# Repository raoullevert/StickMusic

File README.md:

# StickMusic
Stick USB Radio FM/AM/MP3 Diy

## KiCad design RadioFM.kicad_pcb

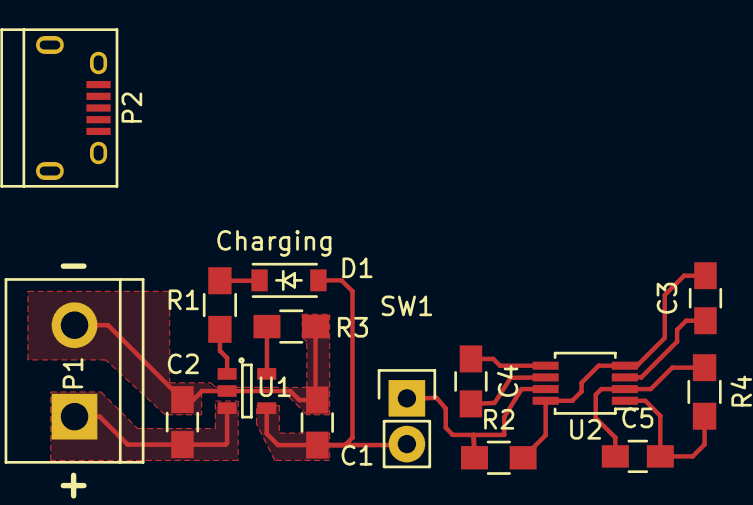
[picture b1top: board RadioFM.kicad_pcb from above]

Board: 2 copper layers, 15 parts (0 on the bottom side), 12 nets.

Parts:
C1, C2: 10u; C_0805_HandSoldering
C3, C5: 10uF; C_0805_HandSoldering
C4: 1uF; C_0805_HandSoldering
D1: Charging; SOD-123
P1: LIPO; bornier2
P2: USB_A; USB_Micro-B
R1: 1K; R_0805_HandSoldering
R2: 100K; R_0805_HandSoldering
R3: 2K; R_0805_HandSoldering
R4: 100k; R_0805_HandSoldering
SW1: SPST; Pin_Header_Straight_1x02
U1: MCP73831; SOT-23-5
U2: MCP1253; MSOP-8_3x3mm_Pitch0.65mm

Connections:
+5V: C5.1, R4.1, U2.2
GND: C1.2, C2.2, C3.2, P1.2, P2.4, R2.2, R3.2, U1.2, U2.4, U2.8
unnamed: C2.1, P1.1, U1.3
unnamed: C3.1, U2.3
unnamed: C4.1, U2.5
unnamed: C4.2, U2.6
unnamed: C5.2, R4.2, U2.1
unnamed: D1.1, R1.1
unnamed: R1.2, U1.1
unnamed: R2.1, SW1.1, U2.7
unnamed: R3.1, U1.5
VCC: C1.1, D1.2, P2.1, SW1.2, U1.4

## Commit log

2015-07-15 nouveau fichier: Controleur.sch nouveau fichier: Datasheets/ADP150-279215.pdf nouveau fichier: Datasheets/MCP73831.pdf nouveau fichier: Datasheets/Si4736-37-38-39-C40.pdf nouveau fichier: Datasheets/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
2015-07-15 nouveau fichier: lisez-moi.txt
